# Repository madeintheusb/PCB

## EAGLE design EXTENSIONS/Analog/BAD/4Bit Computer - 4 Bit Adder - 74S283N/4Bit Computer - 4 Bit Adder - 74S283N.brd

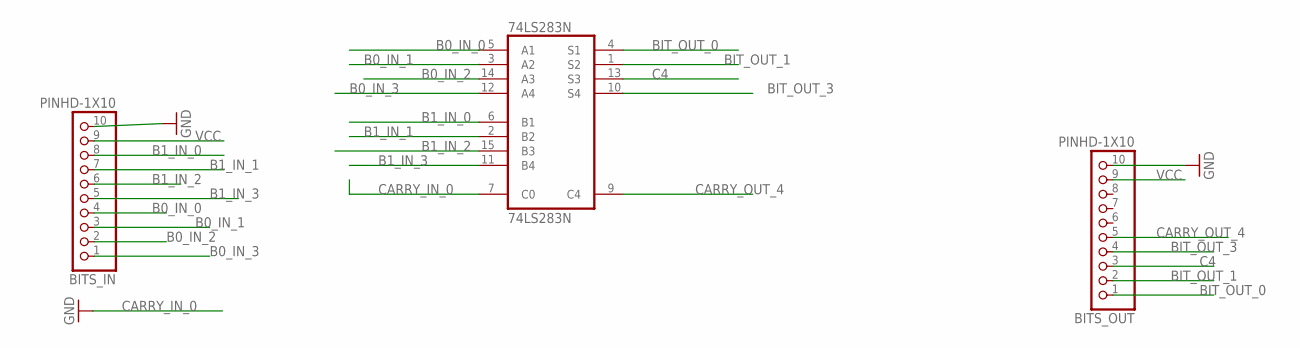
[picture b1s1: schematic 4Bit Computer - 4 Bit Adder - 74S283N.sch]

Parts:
74LS283N: 74LS283N; DIL16
BITS_IN: PINHD-1X10; 1X10-BIG
BITS_OUT: PINHD-1X10; 1X10-BIG

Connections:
B0_IN_0: 74LS283N.5 (A1), BITS_IN.4
B0_IN_1: 74LS283N.3 (A2), BITS_IN.3
B0_IN_2: 74LS283N.14 (A3), BITS_IN.2
B0_IN_3: 74LS283N.12 (A4), BITS_IN.1
B1_IN_0: 74LS283N.6 (B1), BITS_IN.8
B1_IN_1: 74LS283N.2 (B2), BITS_IN.7
B1_IN_2: 74LS283N.15 (B3), BITS_IN.6
B1_IN_3: 74LS283N.11 (B4), BITS_IN.5
BIT_OUT_0: 74LS283N.4 (S1), BITS_OUT.1
BIT_OUT_1: 74LS283N.1 (S2), BITS_OUT.2
BIT_OUT_3: 74LS283N.10 (S4), BITS_OUT.4
C4: 74LS283N.13 (S3), BITS_OUT.3
CARRY_IN_0: 74LS283N.7 (C0)
CARRY_OUT_4: 74LS283N.9 (C4), BITS_OUT.5
GND: 74LS283N.8 (GND), BITS_IN.10, BITS_OUT.10
VCC: 74LS283N.16 (VCC), BITS_IN.9, BITS_OUT.9

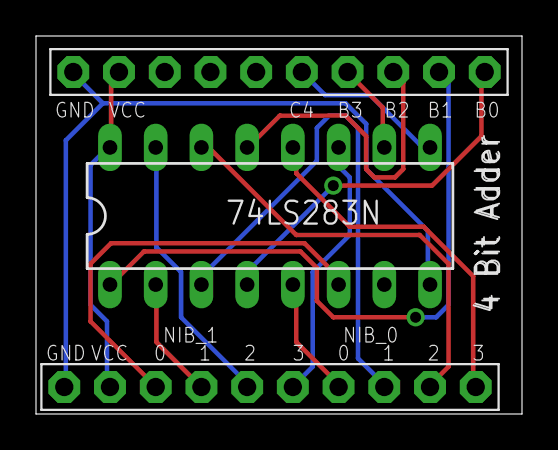
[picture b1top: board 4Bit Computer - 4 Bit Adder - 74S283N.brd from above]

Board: 2 copper layers, 27.0 x 21.0 mm, 3 parts (0 on the bottom side), 15 nets.

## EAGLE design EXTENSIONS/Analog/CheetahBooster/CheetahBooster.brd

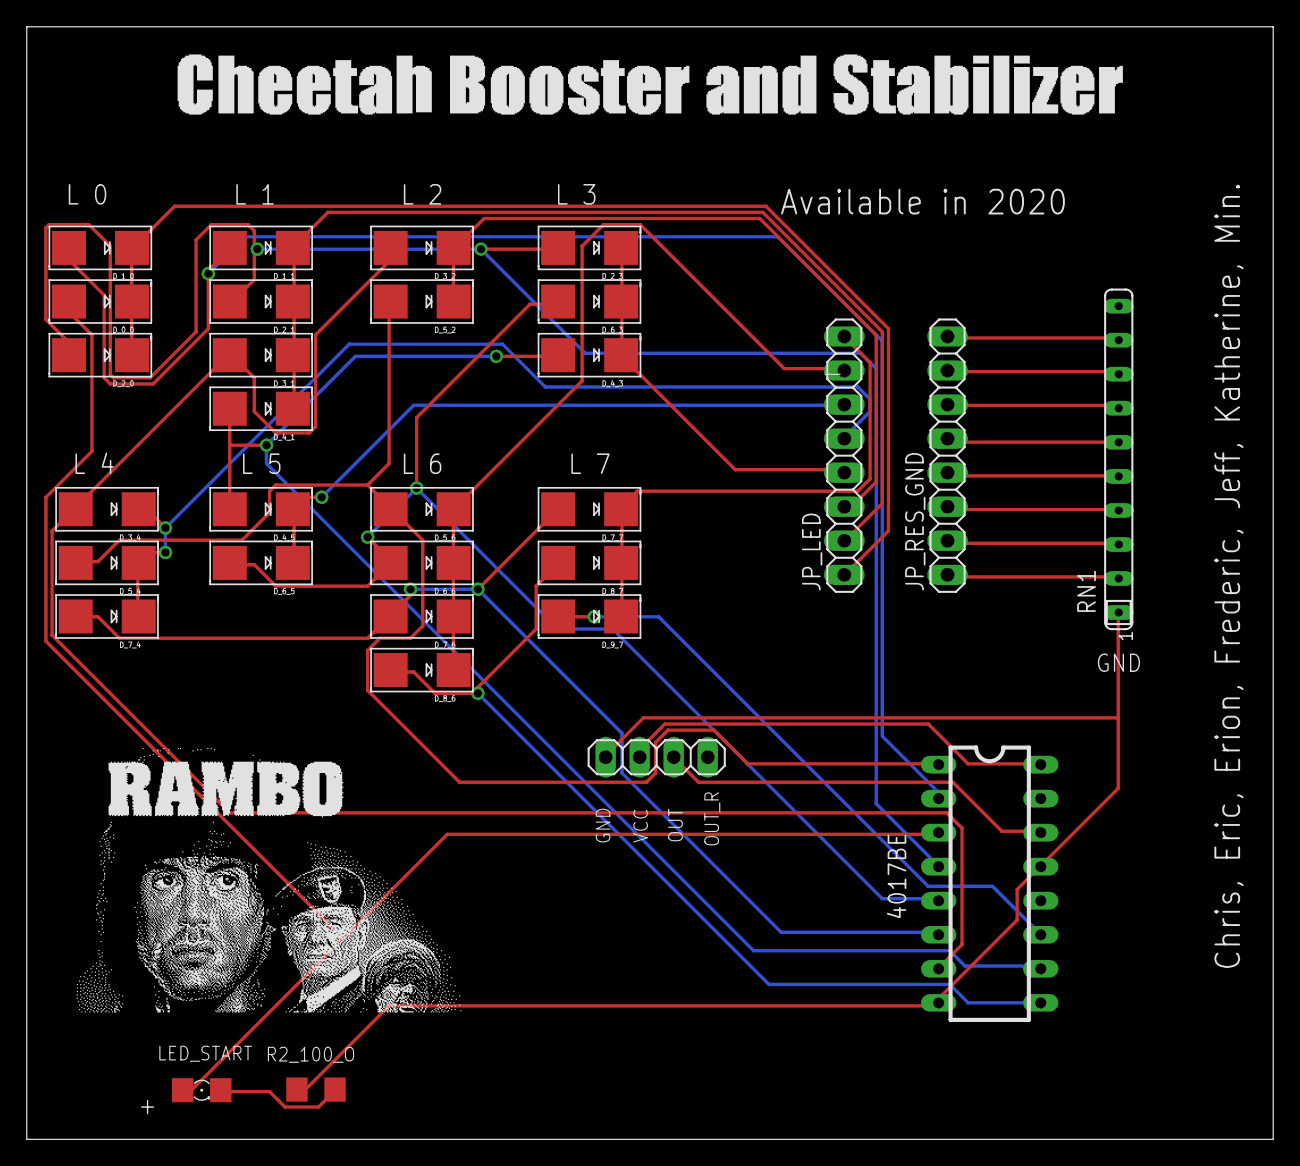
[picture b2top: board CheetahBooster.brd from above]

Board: 2 copper layers, 93.0 x 83.0 mm, 31 parts (0 on the bottom side), 30 nets.

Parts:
4017BE: CD4017; DIL16
D_0_0, D_1_0, D_1_1, D_2_0, D_2_1, D_2_3, D_3_1, D_3_2, D_3_4, D_4_1, D_4_3, D_4_5, D_5_2, D_5_4, D_5_6, D_6_3, D_6_5, D_6_6, D_7_4, D_7_6, D_7_7, D_8_6, D_8_7, D_9_7: SMADIODE
JP_CLOCK_IN: 1X04
JP_LED: 1X08
JP_RES_GND: 1X08
LED_START: 1206
R2_100_O: R1206
RN1: SIP10

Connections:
GND: 4017BE.8, 4017BE.13, JP_CLOCK_IN.1, R2_100_O.1, RN1.1
LED_0: D_0_0.C, D_1_0.C, D_2_0.C, JP_LED.1
LED_1: D_1_1.C, D_2_1.C, D_3_1.C, D_4_1.C, JP_LED.2
LED_2: D_3_2.C, D_5_2.C, JP_LED.3
LED_3: D_2_3.C, D_4_3.C, D_6_3.C, JP_LED.4
LED_4: D_3_4.C, D_5_4.C, D_7_4.C, JP_LED.5
LED_5: D_4_5.C, D_6_5.C, JP_LED.6
LED_6: D_5_6.C, D_6_6.C, D_7_6.C, D_8_6.C, JP_LED.7
LED_7: D_7_7.C, D_8_7.C, D_9_7.C, JP_LED.8
unnamed: LED_START.C, R2_100_O.2
R0: JP_RES_GND.1, RN1.2
R1: JP_RES_GND.2, RN1.3
R2: JP_RES_GND.3, RN1.4
R3: JP_RES_GND.4, RN1.5
R4: JP_RES_GND.5, RN1.6
R5: JP_RES_GND.6, RN1.7
R6: JP_RES_GND.7, RN1.8
R7: JP_RES_GND.8, RN1.9
SEG_0: 4017BE.3, D_0_0.A, LED_START.A
SEG_1: 4017BE.2, D_1_0.A, D_1_1.A
SEG_2: 4017BE.4, D_2_0.A, D_2_1.A, D_2_3.A
SEG_3: 4017BE.7, D_3_1.A, D_3_2.A, D_3_4.A
SEG_4: 4017BE.10, D_4_1.A, D_4_3.A, D_4_5.A
SEG_5: 4017BE.1, D_5_2.A, D_5_4.A, D_5_6.A
SEG_6: 4017BE.5, D_6_3.A, D_6_5.A, D_6_6.A
SEG_7: 4017BE.6, D_7_4.A, D_7_6.A, D_7_7.A
SEG_8: 4017BE.9, D_8_6.A, D_8_7.A
SEG_9: 4017BE.11, D_9_7.A
TMR555_OUTPUT: 4017BE.14, JP_CLOCK_IN.3
VCC: 4017BE.16, JP_CLOCK_IN.2

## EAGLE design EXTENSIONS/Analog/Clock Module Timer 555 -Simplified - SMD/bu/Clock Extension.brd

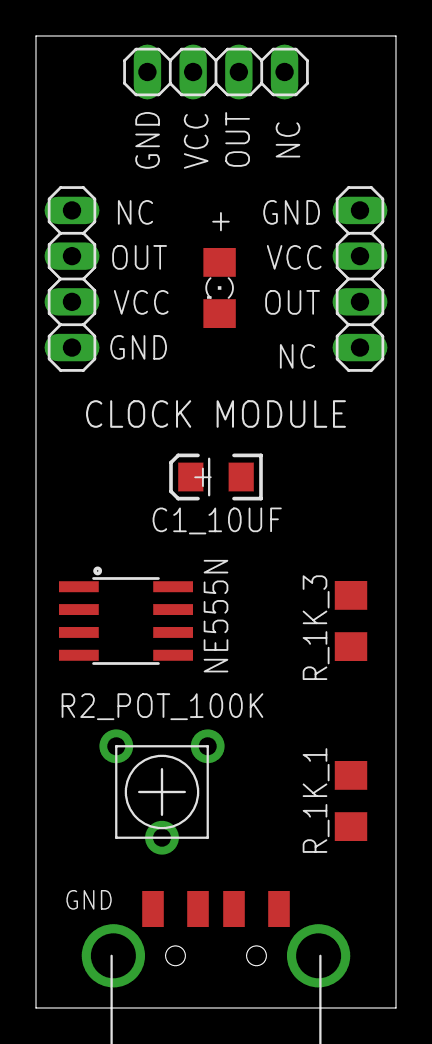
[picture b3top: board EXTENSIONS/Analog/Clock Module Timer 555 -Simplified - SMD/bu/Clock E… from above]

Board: 2 copper layers, 20.0 x 54.0 mm, 10 parts (0 on the bottom side), 6 nets, no tracks yet.

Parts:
C1_10UF: 10uF; EIA3216
LED_OUTPUT: 1206
NE555N: SO08
OUT_1, OUT_2, OUT_3: 1X04
R2_POT_100K: TRIM_POT_PTH
R_1K_1, R_1K_3: R1206
X1: USB-A; MOLEX_480371000

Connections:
DIS: NE555N.7, R2_POT_100K.3, R_1K_1.1
GND: C1_10UF.A, NE555N.1, OUT_1.1, OUT_2.1, OUT_3.1, R_1K_3.1, X1.4
unnamed: LED_OUTPUT.C, R_1K_3.2
THRESHOLD: C1_10UF.C, NE555N.2, NE555N.6, R2_POT_100K.2
TMR555_OUTPUT: LED_OUTPUT.A, NE555N.3, OUT_1.3, OUT_2.3, OUT_3.3
VCC: NE555N.4, NE555N.8, OUT_1.2, OUT_2.2, OUT_3.2, R_1K_1.2, X1.1

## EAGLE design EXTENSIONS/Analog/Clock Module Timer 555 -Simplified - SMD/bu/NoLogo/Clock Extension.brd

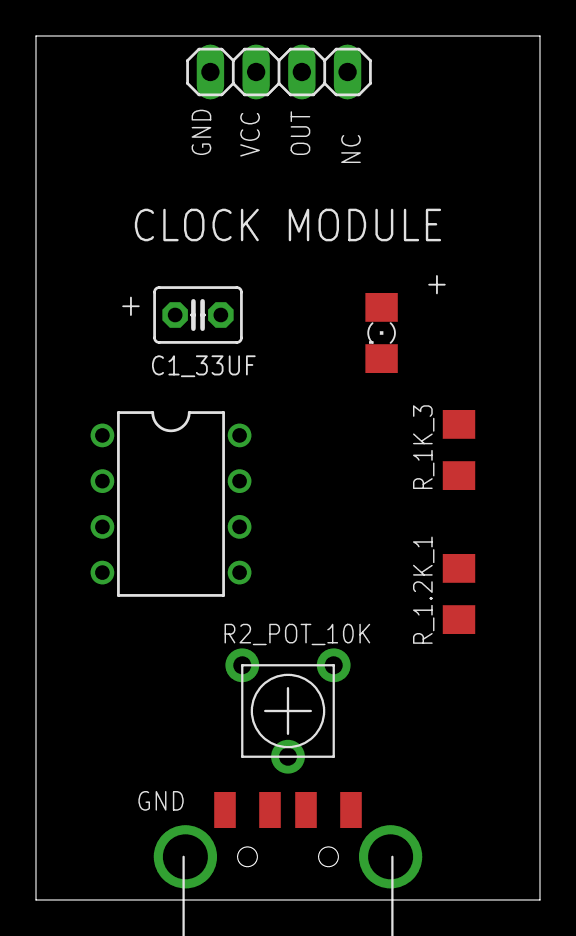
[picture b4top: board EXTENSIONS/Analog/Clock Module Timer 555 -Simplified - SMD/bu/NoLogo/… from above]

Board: 2 copper layers, 28.0 x 48.0 mm, 8 parts (0 on the bottom side), 6 nets, no tracks yet.

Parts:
C1_33UF: C025-030X050
JP1: 1X04
LED_OUTPUT: 1206
R2_POT_10K: TRIM_POT_PTH
R_1.2K_1, R_1K_3: R1206
T555_CLOCK: NE555N; DIL08
X1: USB-A; MOLEX_480371000

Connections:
GND: C1_33UF.1, JP1.1, R_1K_3.1, T555_CLOCK.1, X1.4
unnamed: R2_POT_10K.3, R_1.2K_1.1, T555_CLOCK.7
unnamed: LED_OUTPUT.C, R_1K_3.2
THRESHOLD: C1_33UF.2, R2_POT_10K.2, T555_CLOCK.2, T555_CLOCK.6
TMR555_OUTPUT: JP1.3, LED_OUTPUT.A, T555_CLOCK.3
VCC: JP1.2, R_1.2K_1.2, T555_CLOCK.4, T555_CLOCK.8, X1.1

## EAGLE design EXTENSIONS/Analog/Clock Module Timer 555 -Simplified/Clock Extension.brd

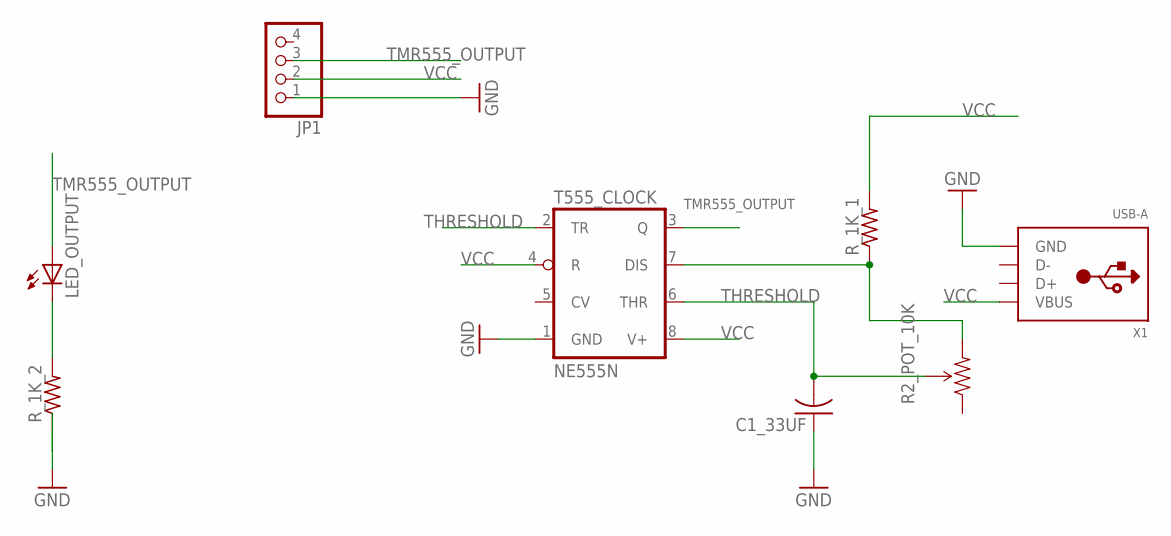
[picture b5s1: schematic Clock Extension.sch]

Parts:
C1_33UF: C-US025-030X050; C025-030X050
JP1: PINHD-1X4; 1X04
LED_OUTPUT: LEDSMT1206; 1206
R2_POT_10K: TRIMPOTPTH; TRIM_POT_PTH
R_1K_1, R_1K_2: R-US_R1206; R1206
T555_CLOCK: NE555N; DIL08
X1: USB-A; MOLEX_480371000

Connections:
GND: C1_33UF.1, JP1.1, R_1K_2.1, T555_CLOCK.1 (GND), X1.4 (GND)
unnamed: R2_POT_10K.3 (CW), R_1K_1.1, T555_CLOCK.7 (DIS)
unnamed: LED_OUTPUT.C, R_1K_2.2
THRESHOLD: C1_33UF.2, R2_POT_10K.2 (WIPER), T555_CLOCK.2 (TR), T555_CLOCK.6 (THR)
TMR555_OUTPUT: JP1.3, LED_OUTPUT.A, T555_CLOCK.3 (Q)
TMR555_OUTPUT_REVERSE: JP1.4
VCC: JP1.2, R_1K_1.2, T555_CLOCK.4 (R), T555_CLOCK.8 (V+), X1.1 (VBUS)

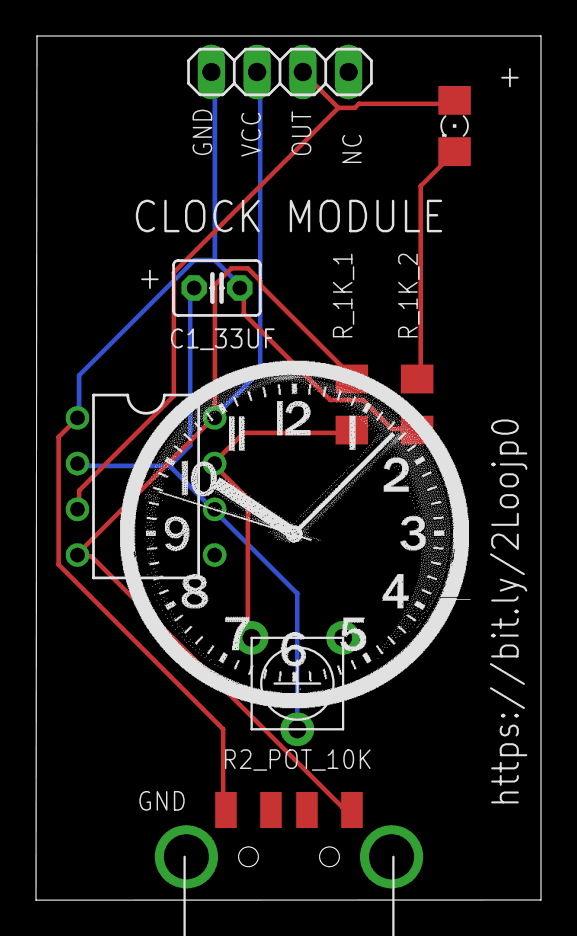
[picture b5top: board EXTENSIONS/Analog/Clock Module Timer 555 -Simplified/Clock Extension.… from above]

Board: 2 copper layers, 28.1 x 48.0 mm, 8 parts (0 on the bottom side), 6 nets.

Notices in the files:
parts and their libraries:
SparkFun-DigitalIC: Licensing: Creative Commons ShareAlike 4.0 International - https://creativecommons.org/licenses/by-sa/4.0
